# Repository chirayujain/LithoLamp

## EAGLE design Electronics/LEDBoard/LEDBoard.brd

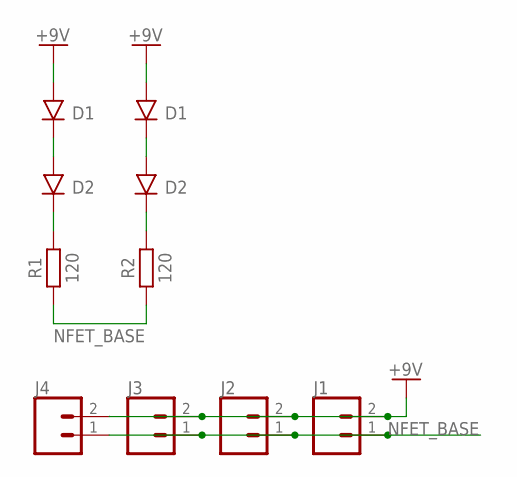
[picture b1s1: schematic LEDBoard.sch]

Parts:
D1, D2, D3, D4: JB3030
J1, J2, J3, J4: CONN_021X02_NO_SILK; 1X02_NO_SILK
R1, R2: 120; RESC2012X65

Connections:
+9V: D1.A, D3.A, J1.2, J2.2, J3.2, J4.2
unnamed: D1.C, D2.A
unnamed: D2.C, R1.2
unnamed: D3.C, D4.A
unnamed: D4.C, R2.2
NFET_BASE: J1.1, J2.1, J3.1, J4.1, R1.1, R2.1

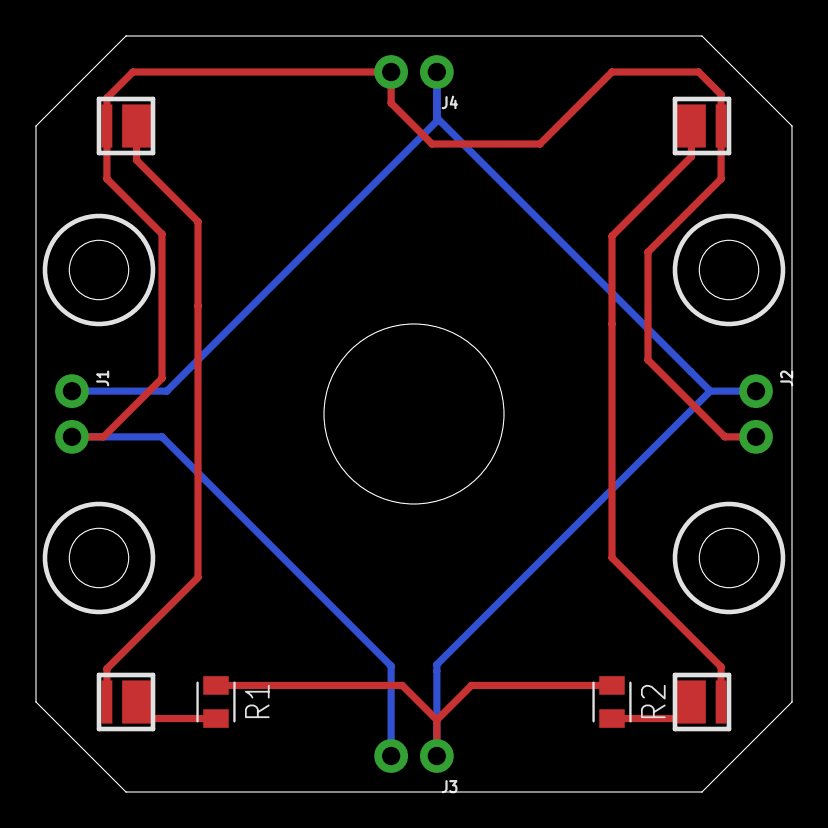
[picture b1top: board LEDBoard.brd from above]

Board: 2 copper layers, 42.0 x 42.0 mm, 10 parts (0 on the bottom side), 6 nets.

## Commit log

2025-01-18 Source Upload
2025-01-18 Create LICENSE

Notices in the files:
parts and their libraries:
SparkFun-Connectors: Licensing: Creative Commons ShareAlike 4.0 International - https://creativecommons.org/licenses/by-sa/4.0
